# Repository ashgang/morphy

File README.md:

# Morphy
Contains the morphy design files and sources codes. The Hardware folder contains the schematics of various versions of the Morphy board and the associated evaluation board. The Software folder consists of the MorphyCore subfolder which contains the core morphy functionality, and the reference implementation of the client library for FreeRTOS.

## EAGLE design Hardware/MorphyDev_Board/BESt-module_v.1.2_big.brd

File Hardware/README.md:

# Morphy Hardware
MorphyPP3_board folder contains the design files for the Morphy PP3 form factor design.
MorphyDev_Board folder contains the design files of the development board for Morphy.

[All design documents including Board Schematics, PCB design and BOM sheets ]

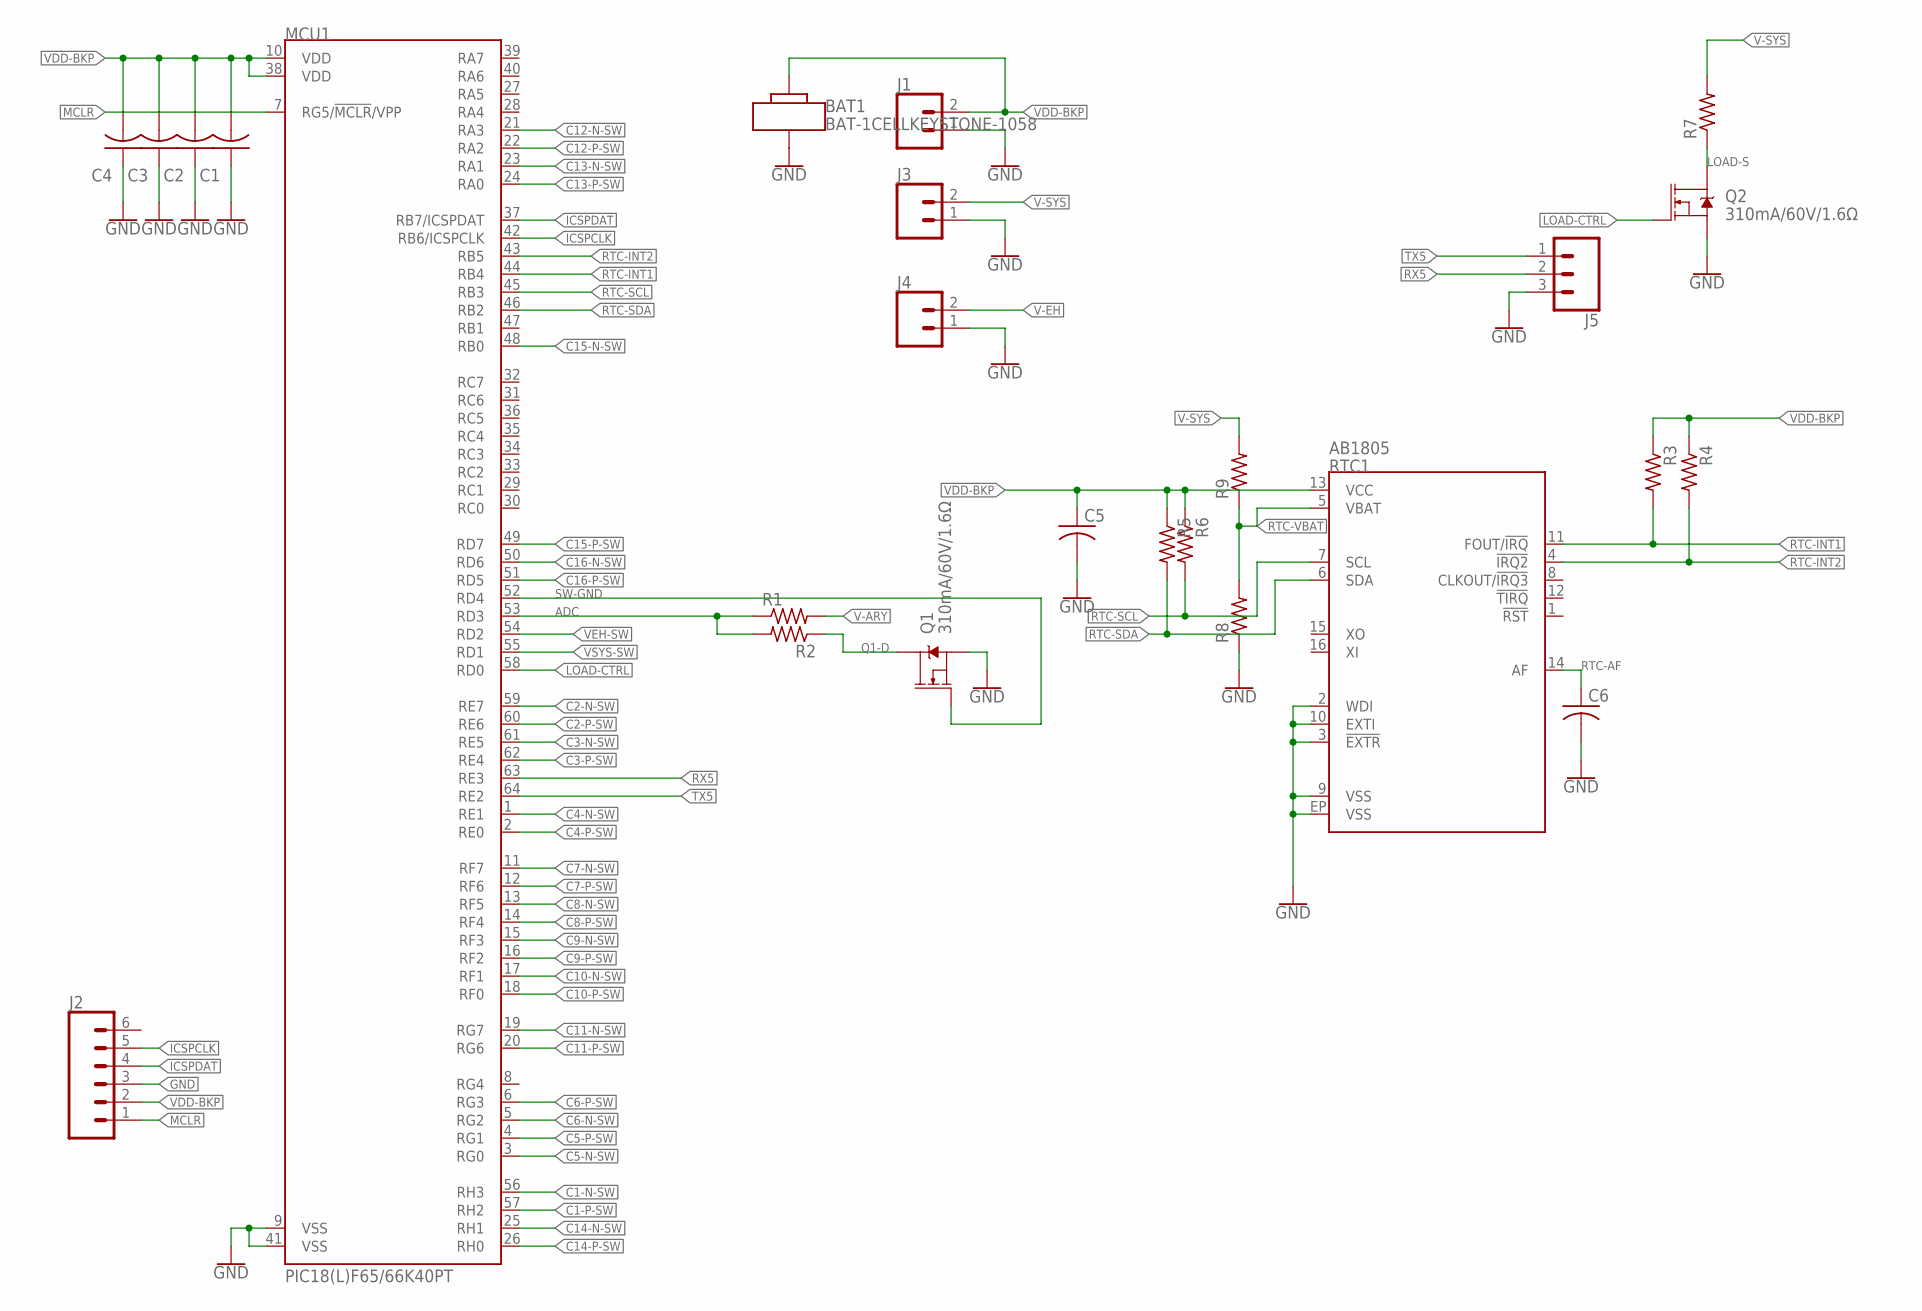
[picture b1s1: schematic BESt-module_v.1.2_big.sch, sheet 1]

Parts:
BAT1: BAT-1CELLKEYSTONE-1058; KEYSTONE-1058
C1, C2, C3, C4: 0.1uF; C0603
C5, C6: C-USC0603; C0603
J1: CONN_02; 1X02
J2: CONN_06NO_SILK_NO_POP; 1X06_NO_SILK
J3, J4: CONN_025MM; SCREWTERMINAL-5MM-2
J5: CONN_03; 1X03
MCU1: PIC18(L)F65/66K40PT; QFP50P1200X1200X120-64N
Q1, Q2: 310mA/60V/1.6Ω; SOT323
R1, R2, R3, R4, R5, R6, R8, R9: R-US_R0603; R0603
R7: R-US_R0805; R0805
RTC1: AB1805; QFN-16-3X3

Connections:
ADC: MCU1.53 (RD3), R1.1, R2.2
C1-N-SW: MCU1.56 (RH3); also elsewhere on the board
C1-P-SW: MCU1.57 (RH2); also elsewhere on the board
C2-N-SW: MCU1.59 (RE7); also elsewhere on the board
C2-P-SW: MCU1.60 (RE6); also elsewhere on the board
C3-N-SW: MCU1.61 (RE5); also elsewhere on the board
C3-P-SW: MCU1.62 (RE4); also elsewhere on the board
C4-N-SW: MCU1.1 (RE1); also elsewhere on the board
C4-P-SW: MCU1.2 (RE0); also elsewhere on the board
C5-N-SW: MCU1.3 (RG0); also elsewhere on the board
C5-P-SW: MCU1.4 (RG1); also elsewhere on the board
C6-N-SW: MCU1.5 (RG2); also elsewhere on the board
C6-P-SW: MCU1.6 (RG3); also elsewhere on the board
C7-N-SW: MCU1.11 (RF7); also elsewhere on the board
C7-P-SW: MCU1.12 (RF6); also elsewhere on the board
C8-N-SW: MCU1.13 (RF5); also elsewhere on the board
C8-P-SW: MCU1.14 (RF4); also elsewhere on the board
C9-N-SW: MCU1.15 (RF3); also elsewhere on the board
C9-P-SW: MCU1.16 (RF2); also elsewhere on the board
C10-N-SW: MCU1.17 (RF1); also elsewhere on the board
C10-P-SW: MCU1.18 (RF0); also elsewhere on the board
C11-N-SW: MCU1.19 (RG7); also elsewhere on the board
C11-P-SW: MCU1.20 (RG6); also elsewhere on the board
C12-N-SW: MCU1.21 (RA3); also elsewhere on the board
C12-P-SW: MCU1.22 (RA2); also elsewhere on the board
C13-N-SW: MCU1.23 (RA1); also elsewhere on the board
C13-P-SW: MCU1.24 (RA0); also elsewhere on the board
C14-N-SW: MCU1.25 (RH1); also elsewhere on the board
C14-P-SW: MCU1.26 (RH0); also elsewhere on the board
C15-N-SW: MCU1.48 (RB0); also elsewhere on the board
C15-P-SW: MCU1.49 (RD7); also elsewhere on the board
C16-N-SW: MCU1.50 (RD6); also elsewhere on the board
C16-P-SW: MCU1.51 (RD5); also elsewhere on the board
GND: BAT1.N, C1.1, C2.1, C3.1, C4.1, C5.2, C6.2, J1.1, J2.3, J3.1, J4.1, J5.3, MCU1.9 (VSS), MCU1.41 (VSS), Q1.2 (S), Q2.2 (S), R8.1, RTC1.2 (WDI), RTC1.3 (!EXTR), RTC1.9 (VSS), RTC1.10 (EXTI), RTC1.EP (VSS); also elsewhere on the board
ICSPCLK: J2.5, MCU1.42 (RB6/ICSPCLK)
ICSPDAT: J2.4, MCU1.37 (RB7/ICSPDAT)
LOAD-CTRL: MCU1.58 (RD0), Q2.1 (G)
LOAD-S: Q2.3 (D), R7.1
MCLR: J2.1, MCU1.7 (RG5/!MCLR!/VPP)
Q1-D: Q1.3 (D), R2.1
RTC-AF: C6.1, RTC1.14 (AF)
RTC-INT1: MCU1.44 (RB4), R3.2, RTC1.11 (FOUT/!IRQ)
RTC-INT2: MCU1.43 (RB5), R4.2, RTC1.4 (!IRQ2)
RTC-SCL: MCU1.45 (RB3), R6.2, RTC1.7 (SCL)
RTC-SDA: MCU1.46 (RB2), R5.2, RTC1.6 (SDA)
RTC-VBAT: R8.2, R9.1, RTC1.5 (VBAT)
RX5: J5.2, MCU1.63 (RE3)
SW-GND: MCU1.52 (RD4), Q1.1 (G)
TX5: J5.1, MCU1.64 (RE2)
V-ARY: R1.2; also elsewhere on the board
V-EH: J4.2; also elsewhere on the board
V-SYS: J3.2, R7.2, R9.2; also elsewhere on the board
VDD-BKP: BAT1.P, C1.2, C2.2, C3.2, C4.2, C5.1, J1.2, J2.2, MCU1.10 (VDD), MCU1.38 (VDD), R3.1, R4.1, R5.1, R6.1, RTC1.13 (VCC); also elsewhere on the board
VEH-SW: MCU1.54 (RD2); also elsewhere on the board
VSYS-SW: MCU1.55 (RD1); also elsewhere on the board

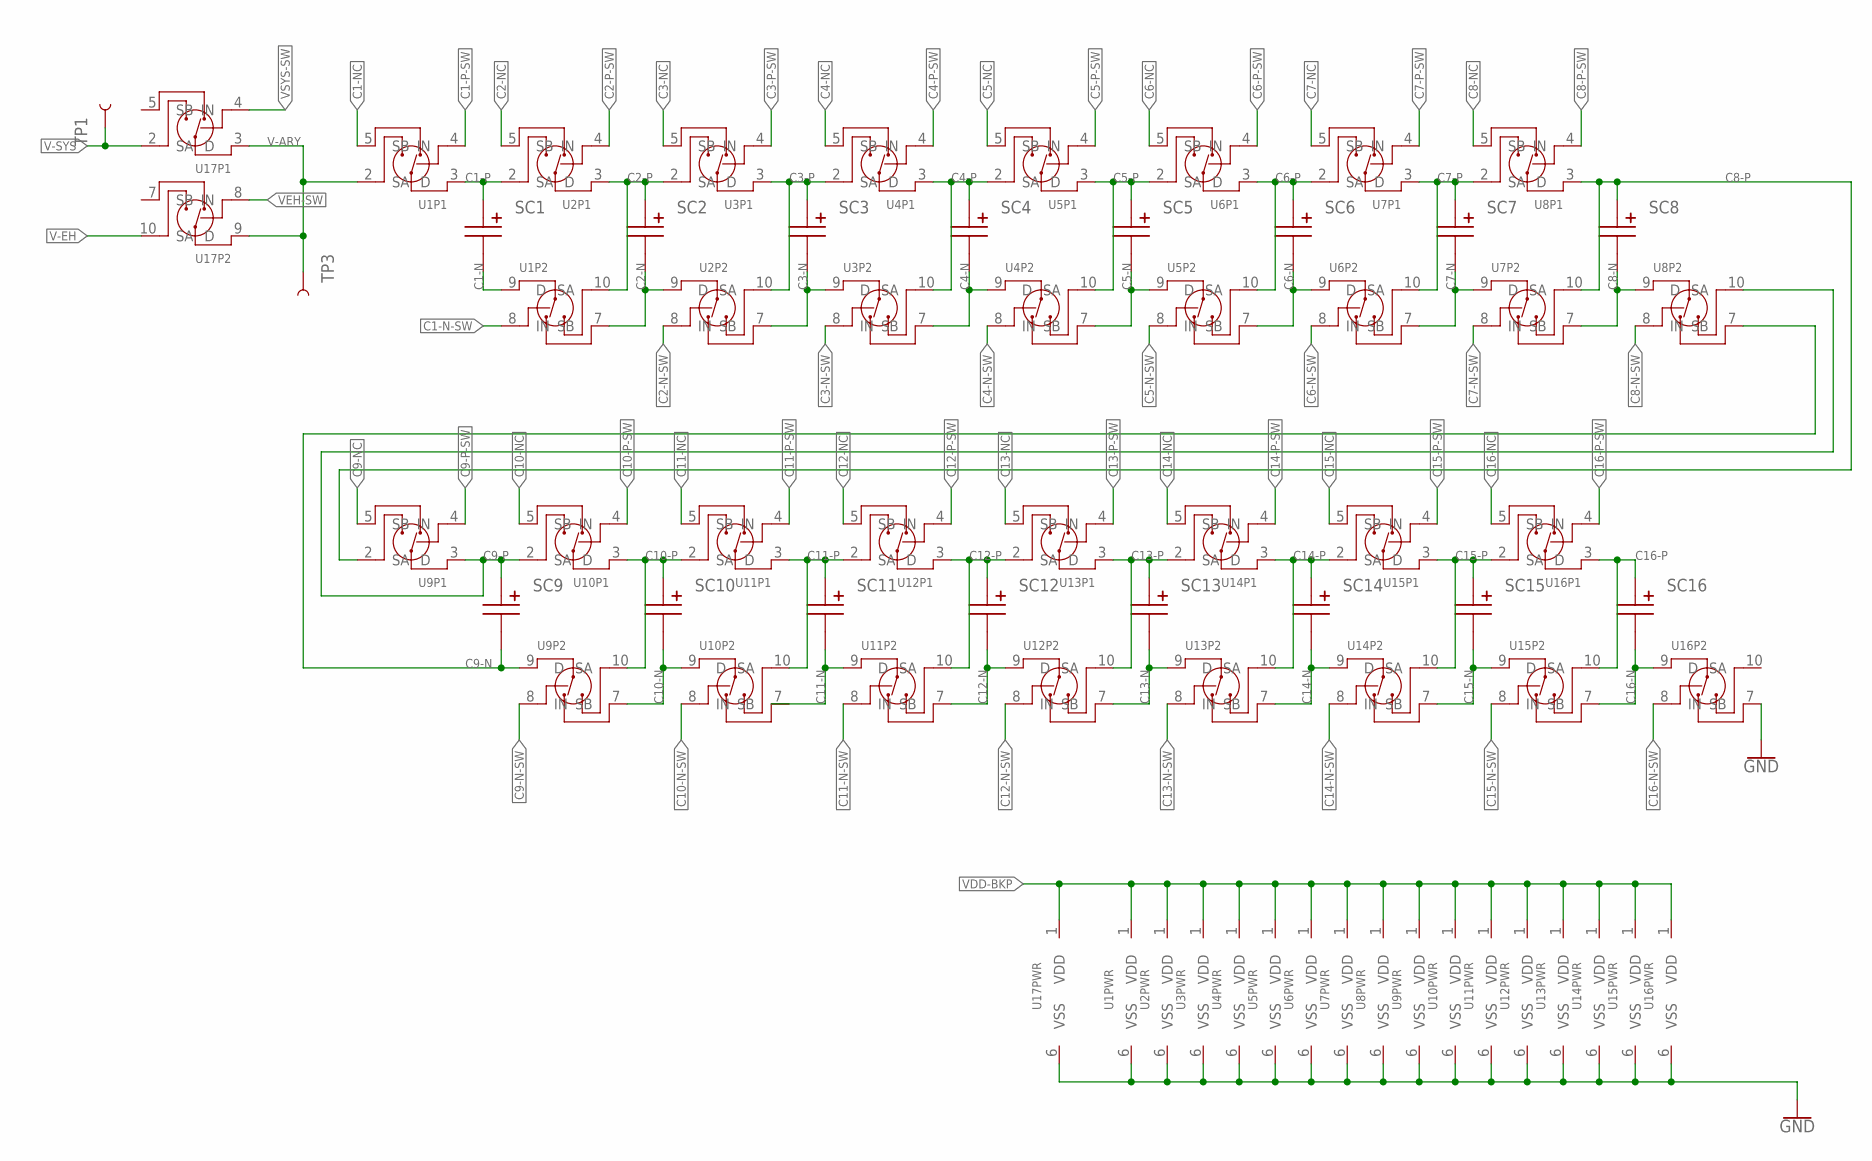
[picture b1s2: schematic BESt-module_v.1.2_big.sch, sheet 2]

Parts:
SC1, SC2, SC3, SC4, SC5, SC6, SC7, SC8, SC9, SC10, SC11, SC12, SC13, SC14, SC15, SC16: PM-5R0H/V104-R-VER; EATON-13X11.3X6-V
TP1, TP3: TEST-POINT3X4; PAD.03X.04
U1, U2, U3, U4, U5, U6, U7, U8, U9, U10, U11, U12, U13, U14, U15, U16, U17: DG2535EDQ; SOP50P490X110-10N

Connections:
C1-N: SC1.N, U1.9 (D)
C1-N-SW: U1.8 (IN); also elsewhere on the board
C1-NC: U1.5 (SB)
C1-P: SC1.P, U1.3 (D), U2.2 (SA)
C1-P-SW: U1.4 (IN); also elsewhere on the board
C2-N: SC2.N, U1.7 (SB), U2.9 (D)
C2-N-SW: U2.8 (IN); also elsewhere on the board
C2-NC: U2.5 (SB)
C2-P: SC2.P, U1.10 (SA), U2.3 (D), U3.2 (SA)
C2-P-SW: U2.4 (IN); also elsewhere on the board
C3-N: SC3.N, U2.7 (SB), U3.9 (D)
C3-N-SW: U3.8 (IN); also elsewhere on the board
C3-NC: U3.5 (SB)
C3-P: SC3.P, U2.10 (SA), U3.3 (D), U4.2 (SA)
C3-P-SW: U3.4 (IN); also elsewhere on the board
C4-N: SC4.N, U3.7 (SB), U4.9 (D)
C4-N-SW: U4.8 (IN); also elsewhere on the board
C4-NC: U4.5 (SB)
C4-P: SC4.P, U3.10 (SA), U4.3 (D), U5.2 (SA)
C4-P-SW: U4.4 (IN); also elsewhere on the board
C5-N: SC5.N, U4.7 (SB), U5.9 (D)
C5-N-SW: U5.8 (IN); also elsewhere on the board
C5-NC: U5.5 (SB)
C5-P: SC5.P, U4.10 (SA), U5.3 (D), U6.2 (SA)
C5-P-SW: U5.4 (IN); also elsewhere on the board
C6-N: SC6.N, U5.7 (SB), U6.9 (D)
C6-N-SW: U6.8 (IN); also elsewhere on the board
C6-NC: U6.5 (SB)
C6-P: SC6.P, U5.10 (SA), U6.3 (D), U7.2 (SA)
C6-P-SW: U6.4 (IN); also elsewhere on the board
C7-N: SC7.N, U6.7 (SB), U7.9 (D)
C7-N-SW: U7.8 (IN); also elsewhere on the board
C7-NC: U7.5 (SB)
C7-P: SC7.P, U6.10 (SA), U7.3 (D), U8.2 (SA)
C7-P-SW: U7.4 (IN); also elsewhere on the board
C8-N: SC8.N, U7.7 (SB), U8.9 (D)
C8-N-SW: U8.8 (IN); also elsewhere on the board
C8-NC: U8.5 (SB)
C8-P: SC8.P, U7.10 (SA), U8.3 (D), U9.2 (SA)
C8-P-SW: U8.4 (IN); also elsewhere on the board
C9-N: SC9.N, U8.7 (SB), U9.9 (D)
C9-N-SW: U9.8 (IN); also elsewhere on the board
C9-NC: U9.5 (SB)
C9-P: SC9.P, U8.10 (SA), U9.3 (D), U10.2 (SA)
C9-P-SW: U9.4 (IN); also elsewhere on the board
C10-N: SC10.N, U9.7 (SB), U10.9 (D)
C10-N-SW: U10.8 (IN); also elsewhere on the board
C10-NC: U10.5 (SB)
C10-P: SC10.P, U9.10 (SA), U10.3 (D), U11.2 (SA)
C10-P-SW: U10.4 (IN); also elsewhere on the board
C11-N: SC11.N, U10.7 (SB), U11.9 (D)
C11-N-SW: U11.8 (IN); also elsewhere on the board
C11-NC: U11.5 (SB)
C11-P: SC11.P, U10.10 (SA), U11.3 (D), U12.2 (SA)
C11-P-SW: U11.4 (IN); also elsewhere on the board
C12-N: SC12.N, U11.7 (SB), U12.9 (D)
C12-N-SW: U12.8 (IN); also elsewhere on the board
C12-NC: U12.5 (SB)
C12-P: SC12.P, U11.10 (SA), U12.3 (D), U13.2 (SA)
C12-P-SW: U12.4 (IN); also elsewhere on the board
C13-N: SC13.N, U12.7 (SB), U13.9 (D)
C13-N-SW: U13.8 (IN); also elsewhere on the board
C13-NC: U13.5 (SB)
C13-P: SC13.P, U12.10 (SA), U13.3 (D), U14.2 (SA)
C13-P-SW: U13.4 (IN); also elsewhere on the board
C14-N: SC14.N, U13.7 (SB), U14.9 (D)
C14-N-SW: U14.8 (IN); also elsewhere on the board
C14-NC: U14.5 (SB)
C14-P: SC14.P, U13.10 (SA), U14.3 (D), U15.2 (SA)
C14-P-SW: U14.4 (IN); also elsewhere on the board
C15-N: SC15.N, U14.7 (SB), U15.9 (D)
C15-N-SW: U15.8 (IN); also elsewhere on the board
C15-NC: U15.5 (SB)
C15-P: SC15.P, U14.10 (SA), U15.3 (D), U16.2 (SA)
C15-P-SW: U15.4 (IN); also elsewhere on the board
C16-N: SC16.N, U15.7 (SB), U16.9 (D)
C16-N-SW: U16.8 (IN); also elsewhere on the board
C16-NC: U16.5 (SB)
C16-P: SC16.P, U15.10 (SA), U16.3 (D)
C16-P-SW: U16.4 (IN); also elsewhere on the board
GND: U1.6 (VSS), U2.6 (VSS), U3.6 (VSS), U4.6 (VSS), U5.6 (VSS), U6.6 (VSS), U7.6 (VSS), U8.6 (VSS), U9.6 (VSS), U10.6 (VSS), U11.6 (VSS), U12.6 (VSS), U13.6 (VSS), U14.6 (VSS), U15.6 (VSS), U16.6 (VSS), U16.7 (SB), U17.6 (VSS); also elsewhere on the board
V-ARY: TP3.P$1, U1.2 (SA), U17.3 (D), U17.9 (D); also elsewhere on the board
V-EH: U17.10 (SA); also elsewhere on the board
V-SYS: TP1.P$1, U17.2 (SA); also elsewhere on the board
VDD-BKP: U1.1 (VDD), U2.1 (VDD), U3.1 (VDD), U4.1 (VDD), U5.1 (VDD), U6.1 (VDD), U7.1 (VDD), U8.1 (VDD), U9.1 (VDD), U10.1 (VDD), U11.1 (VDD), U12.1 (VDD), U13.1 (VDD), U14.1 (VDD), U15.1 (VDD), U16.1 (VDD), U17.1 (VDD); also elsewhere on the board
VEH-SW: U17.8 (IN); also elsewhere on the board
VSYS-SW: U17.4 (IN); also elsewhere on the board

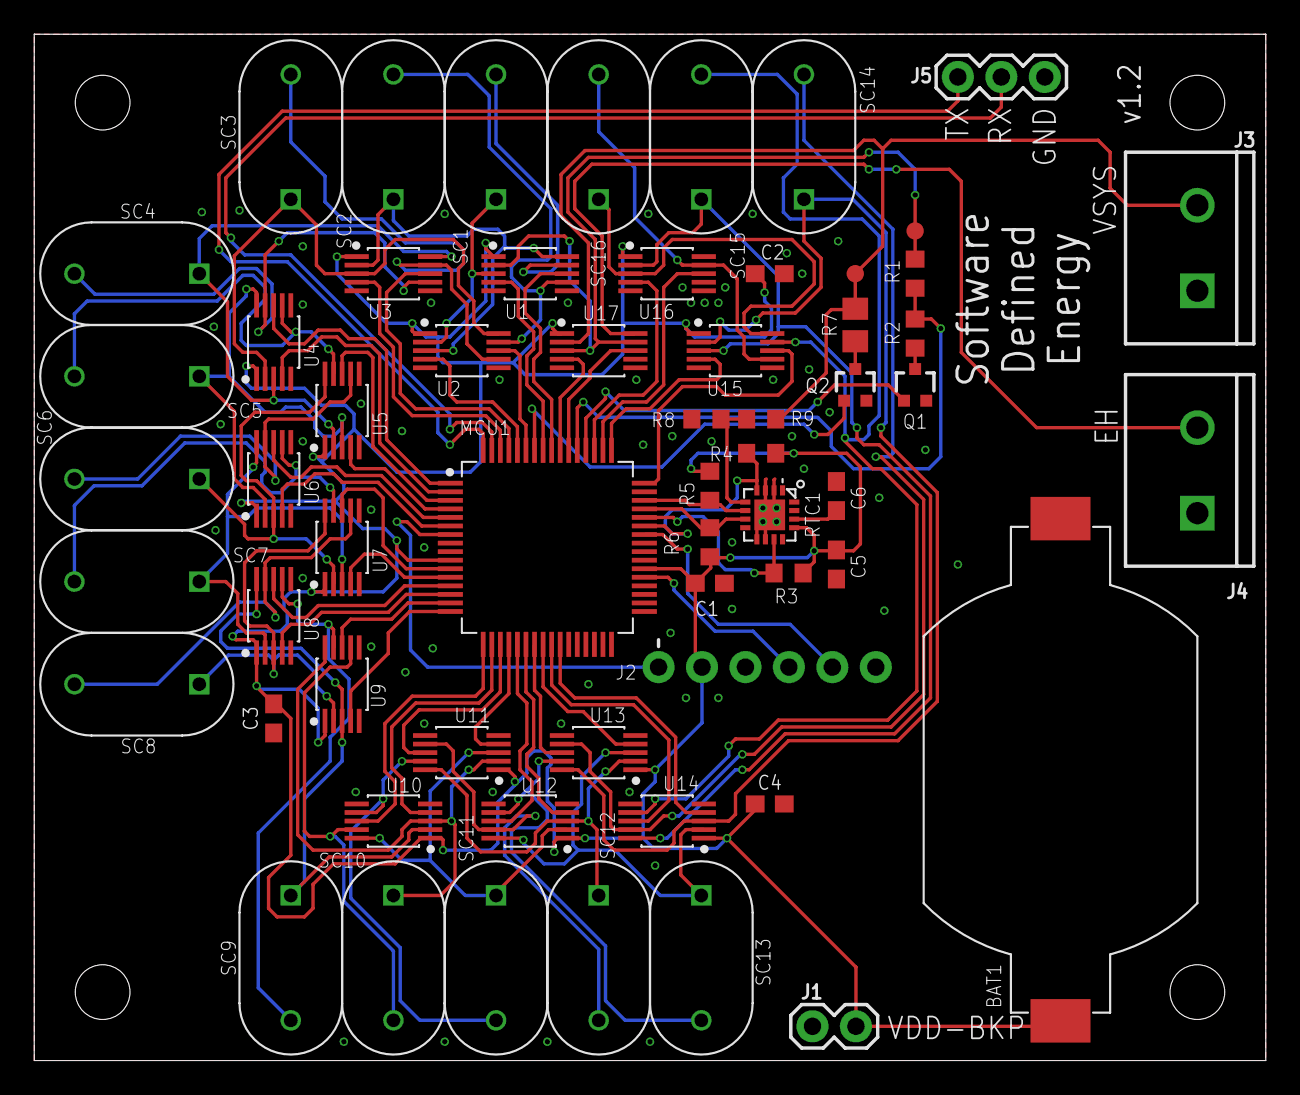
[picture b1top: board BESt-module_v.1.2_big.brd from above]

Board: 2 copper layers, 72.0 x 60.0 mm, 60 parts (0 on the bottom side), 87 nets.

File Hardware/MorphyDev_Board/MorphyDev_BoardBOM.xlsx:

Comment | Description | Designator | Footprint | LibRef | Quantity
BAT-1CELLKEYSTONE-1058 |  | BAT1 | KEYSTONE-1058 | BAT-1CELLKEYSTONE-1058 | 1
0.1uF | CAPACITOR, American symbol | C1, C2, C3, C4 | C0603 | C-USC0603 | 4
C-USC0603 | CAPACITOR, American symbol | C5, C6 | C0603 | C-USC0603 | 2
CONN_02 | Multi connection point. Often used as Generic Header-pin footprint for 0.1 inch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 | J1 | 1X02 | CONN_02 | 1
CONN_06NO_SILK_NO_POP | Multi connection point. Often used as Generic Header-pin footprint for 0.1 inch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 | J2 | 1X06_NO_SILK | CONN_06NO_SILK_NO_POP | 1
CONN_025MM | Multi connection point. Often used as Generic Header-pin footprint for 0.1 inch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 | J3, J4 | SCREWTERMINAL-5MM-2 | CONN_025MM | 2
CONN_03 | Multi connection point. Often used as Generic Header-pin footprint for 0.1 inch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 | J5 | 1X03 | CONN_03 | 1
PIC18(L)F65/66K40PT | 64-Pin, Low-Power, High-Performance Microcontrollers with XLP Technology | MCU1 | QFP50P1200X1200X120-64N | PIC18(L)F65/66K40PT | 1
310mA/60V/1.6Ω | N-channel MOSFETs Voltage controlled devices that allow control of high current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 | Q1, Q2 | SOT323 | MOSFET-NCH-2N7002PW | 2
R-US_R0603 | RESISTOR, American symbol | R1, R2, R3, R4, R5, R6, R8, R9 | R0603 | R-US_R0603 | 8
R-US_R0805 | RESISTOR, American symbol | R7 | R0805 | R-US_R0805 | 1
AB1805 |  | RTC1 | QFN-16-3X3 | AB1805 | 1
PM-5R0H/V104-R-VER | CAP 100MF -20% +80% 5V T/H | SC1, SC2, SC3, SC4, SC5, SC6, SC7, SC8, SC9, SC10, SC11, SC12, SC13, SC14, SC15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 | EATON-13X11.3X6-V | PM-5R0H/V104-R-VER | 16
TEST-POINT3X4 | SparkFun Test Points Bare copper test points for troubleshooting or In-Circuit-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 | TP1, TP3 | PAD.03X.04 | TEST-POINT3X4 | 2
DG2535EDQ | IC ANALOG SWITCH DUAL | U1, U2, U3, U4, U5, U6, U7, U8, U9, U10, U11, U12, U13, U14, U15, U16, U17 | SOP50P490X110-10N | DG2535EDQ | 17

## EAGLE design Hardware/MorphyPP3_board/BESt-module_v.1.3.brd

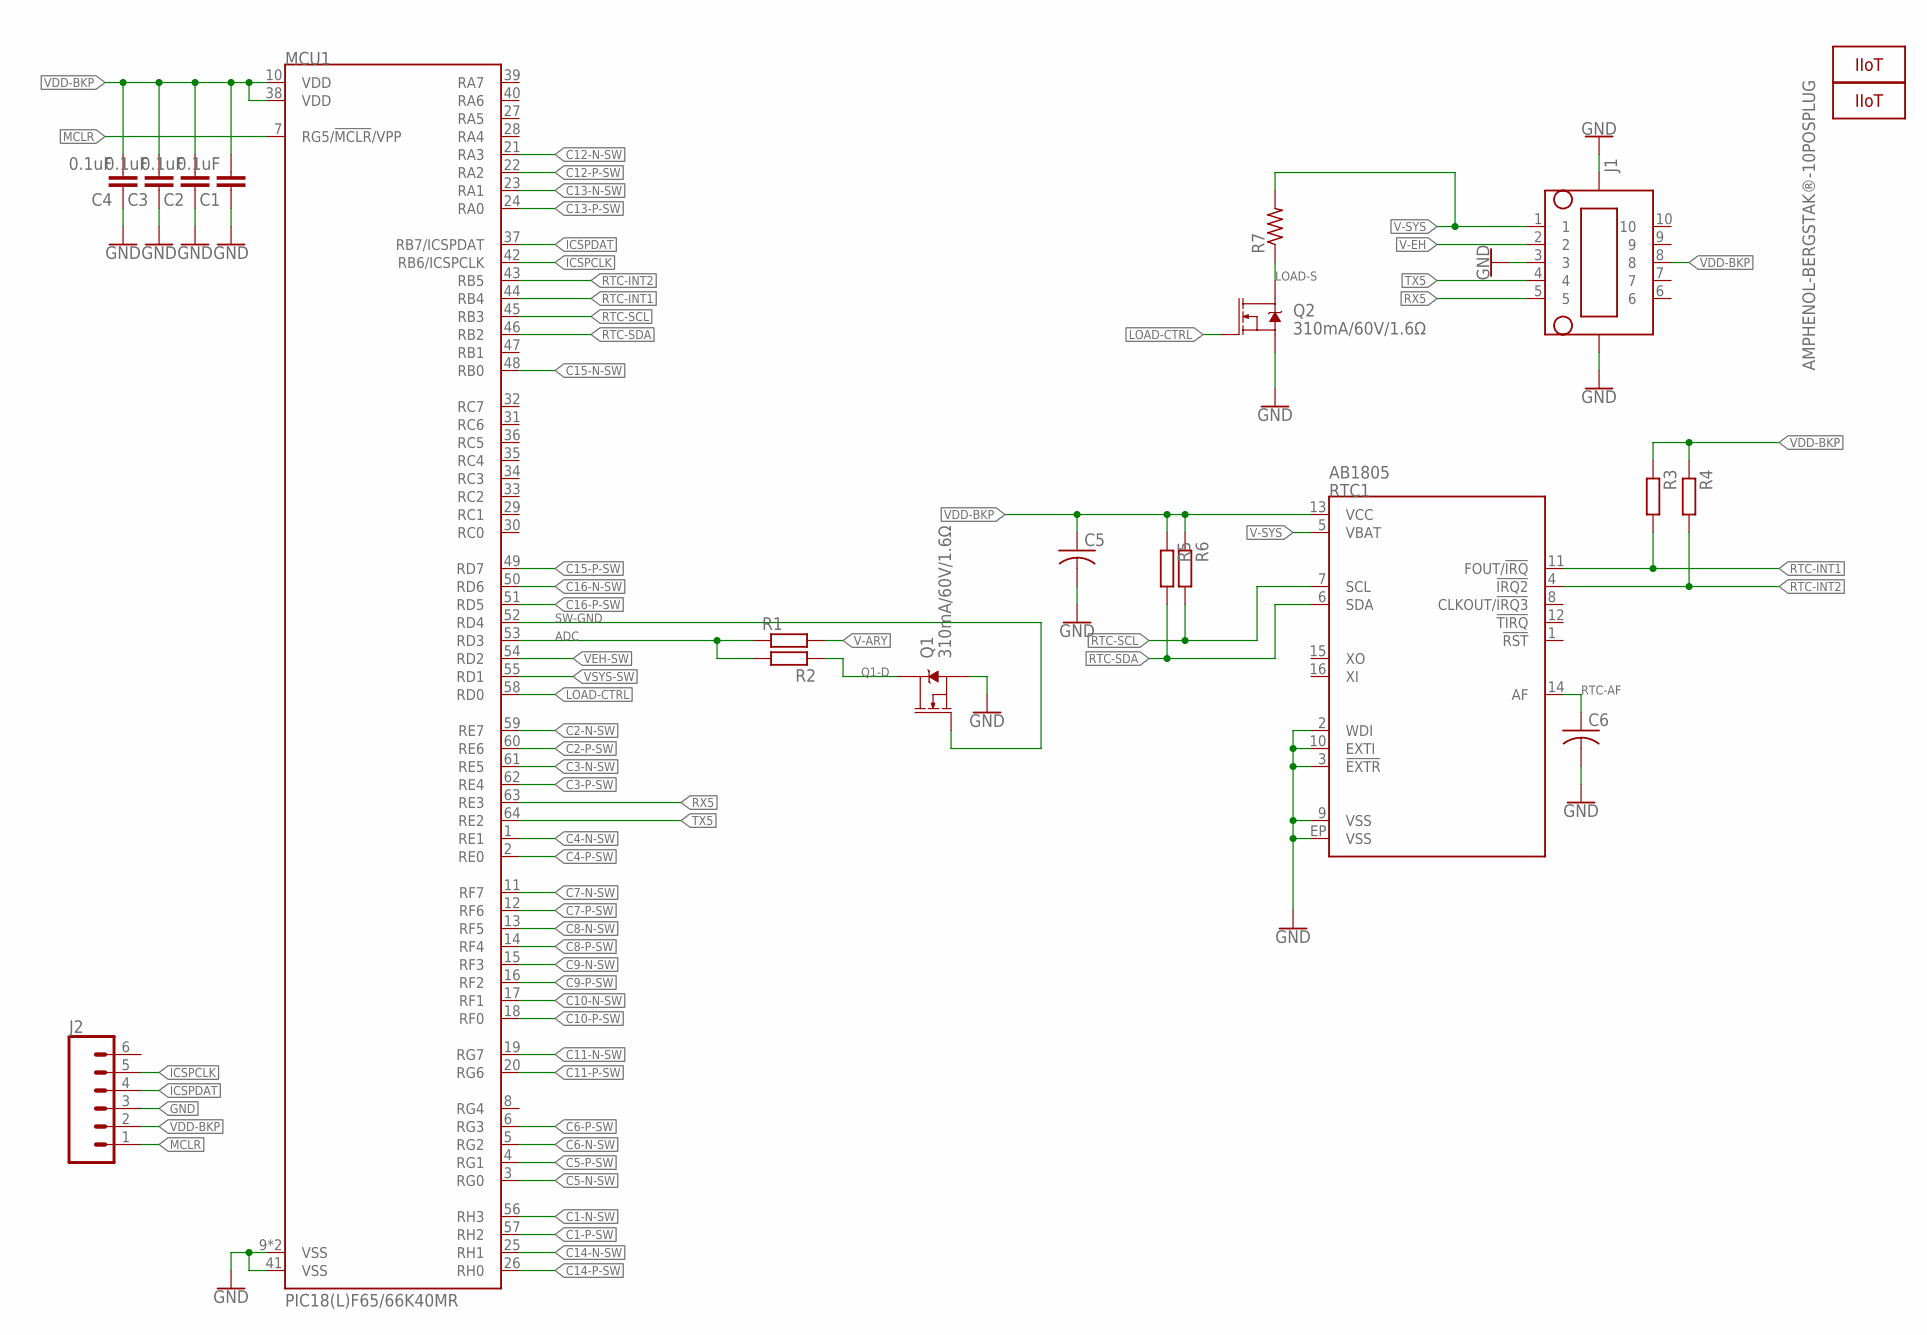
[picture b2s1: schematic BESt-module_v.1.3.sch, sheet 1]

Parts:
C1, C2, C3, C4: 0.1uF; 0603
C5, C6: C-USC0402; C0402
J1: AMPHENOL-BERGSTAK®-10POSPLUG; 10132797-10POS-PLUG
J2: CONN_06NO_SILK_NO_POP; 1X06_NO_SILK
LOGO1, LOGO2: IIOT
MCU1: PIC18(L)F65/66K40MR; QFN50P900X900X100-65T715N
Q1, Q2: 310mA/60V/1.6Ω; SOT323
R1, R2, R3, R4, R5, R6: R-EU_R0402; R0402
R7: R-US_R0805; R0805
RTC1: AB1805; QFN-16-3X3

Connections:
ADC: MCU1.53 (RD3), R1.1, R2.2
C1-N-SW: MCU1.56 (RH3); also elsewhere on the board
C1-P-SW: MCU1.57 (RH2); also elsewhere on the board
C2-N-SW: MCU1.59 (RE7); also elsewhere on the board
C2-P-SW: MCU1.60 (RE6); also elsewhere on the board
C3-N-SW: MCU1.61 (RE5); also elsewhere on the board
C3-P-SW: MCU1.62 (RE4); also elsewhere on the board
C4-N-SW: MCU1.1 (RE1); also elsewhere on the board
C4-P-SW: MCU1.2 (RE0); also elsewhere on the board
C5-N-SW: MCU1.3 (RG0); also elsewhere on the board
C5-P-SW: MCU1.4 (RG1); also elsewhere on the board
C6-N-SW: MCU1.5 (RG2); also elsewhere on the board
C6-P-SW: MCU1.6 (RG3); also elsewhere on the board
C7-N-SW: MCU1.11 (RF7); also elsewhere on the board
C7-P-SW: MCU1.12 (RF6); also elsewhere on the board
C8-N-SW: MCU1.13 (RF5); also elsewhere on the board
C8-P-SW: MCU1.14 (RF4); also elsewhere on the board
C9-N-SW: MCU1.15 (RF3); also elsewhere on the board
C9-P-SW: MCU1.16 (RF2); also elsewhere on the board
C10-N-SW: MCU1.17 (RF1); also elsewhere on the board
C10-P-SW: MCU1.18 (RF0); also elsewhere on the board
C11-N-SW: MCU1.19 (RG7); also elsewhere on the board
C11-P-SW: MCU1.20 (RG6); also elsewhere on the board
C12-N-SW: MCU1.21 (RA3); also elsewhere on the board
C12-P-SW: MCU1.22 (RA2); also elsewhere on the board
C13-N-SW: MCU1.23 (RA1); also elsewhere on the board
C13-P-SW: MCU1.24 (RA0); also elsewhere on the board
C14-N-SW: MCU1.25 (RH1); also elsewhere on the board
C14-P-SW: MCU1.26 (RH0); also elsewhere on the board
C15-N-SW: MCU1.48 (RB0); also elsewhere on the board
C15-P-SW: MCU1.49 (RD7); also elsewhere on the board
C16-N-SW: MCU1.50 (RD6); also elsewhere on the board
C16-P-SW: MCU1.51 (RD5); also elsewhere on the board
GND: C1.1, C2.1, C3.1, C4.1, C5.2, C6.2, J1.3, J1.MNT1, J1.MNT2, J2.3, MCU1.9 (VSS), MCU1.41 (VSS), MCU1.65 (VSS), Q1.2 (S), Q2.2 (S), RTC1.2 (WDI), RTC1.3 (!EXTR), RTC1.9 (VSS), RTC1.10 (EXTI), RTC1.EP (VSS); also elsewhere on the board
ICSPCLK: J2.5, MCU1.42 (RB6/ICSPCLK)
ICSPDAT: J2.4, MCU1.37 (RB7/ICSPDAT)
LOAD-CTRL: MCU1.58 (RD0), Q2.1 (G)
LOAD-S: Q2.3 (D), R7.1
MCLR: J2.1, MCU1.7 (RG5/!MCLR!/VPP)
Q1-D: Q1.3 (D), R2.1
RTC-AF: C6.1, RTC1.14 (AF)
RTC-INT1: MCU1.44 (RB4), R3.2, RTC1.11 (FOUT/!IRQ)
RTC-INT2: MCU1.43 (RB5), R4.2, RTC1.4 (!IRQ2)
RTC-SCL: MCU1.45 (RB3), R6.2, RTC1.7 (SCL)
RTC-SDA: MCU1.46 (RB2), R5.2, RTC1.6 (SDA)
RX5: J1.5, MCU1.63 (RE3)
SW-GND: MCU1.52 (RD4), Q1.1 (G)
TX5: J1.4, MCU1.64 (RE2)
V-ARY: R1.2; also elsewhere on the board
V-EH: J1.2; also elsewhere on the board
V-SYS: J1.1, R7.2, RTC1.5 (VBAT); also elsewhere on the board
VDD-BKP: C1.2, C2.2, C3.2, C4.2, C5.1, J1.8, J2.2, MCU1.10 (VDD), MCU1.38 (VDD), R3.1, R4.1, R5.1, R6.1, RTC1.13 (VCC); also elsewhere on the board
VEH-SW: MCU1.54 (RD2); also elsewhere on the board
VSYS-SW: MCU1.55 (RD1); also elsewhere on the board

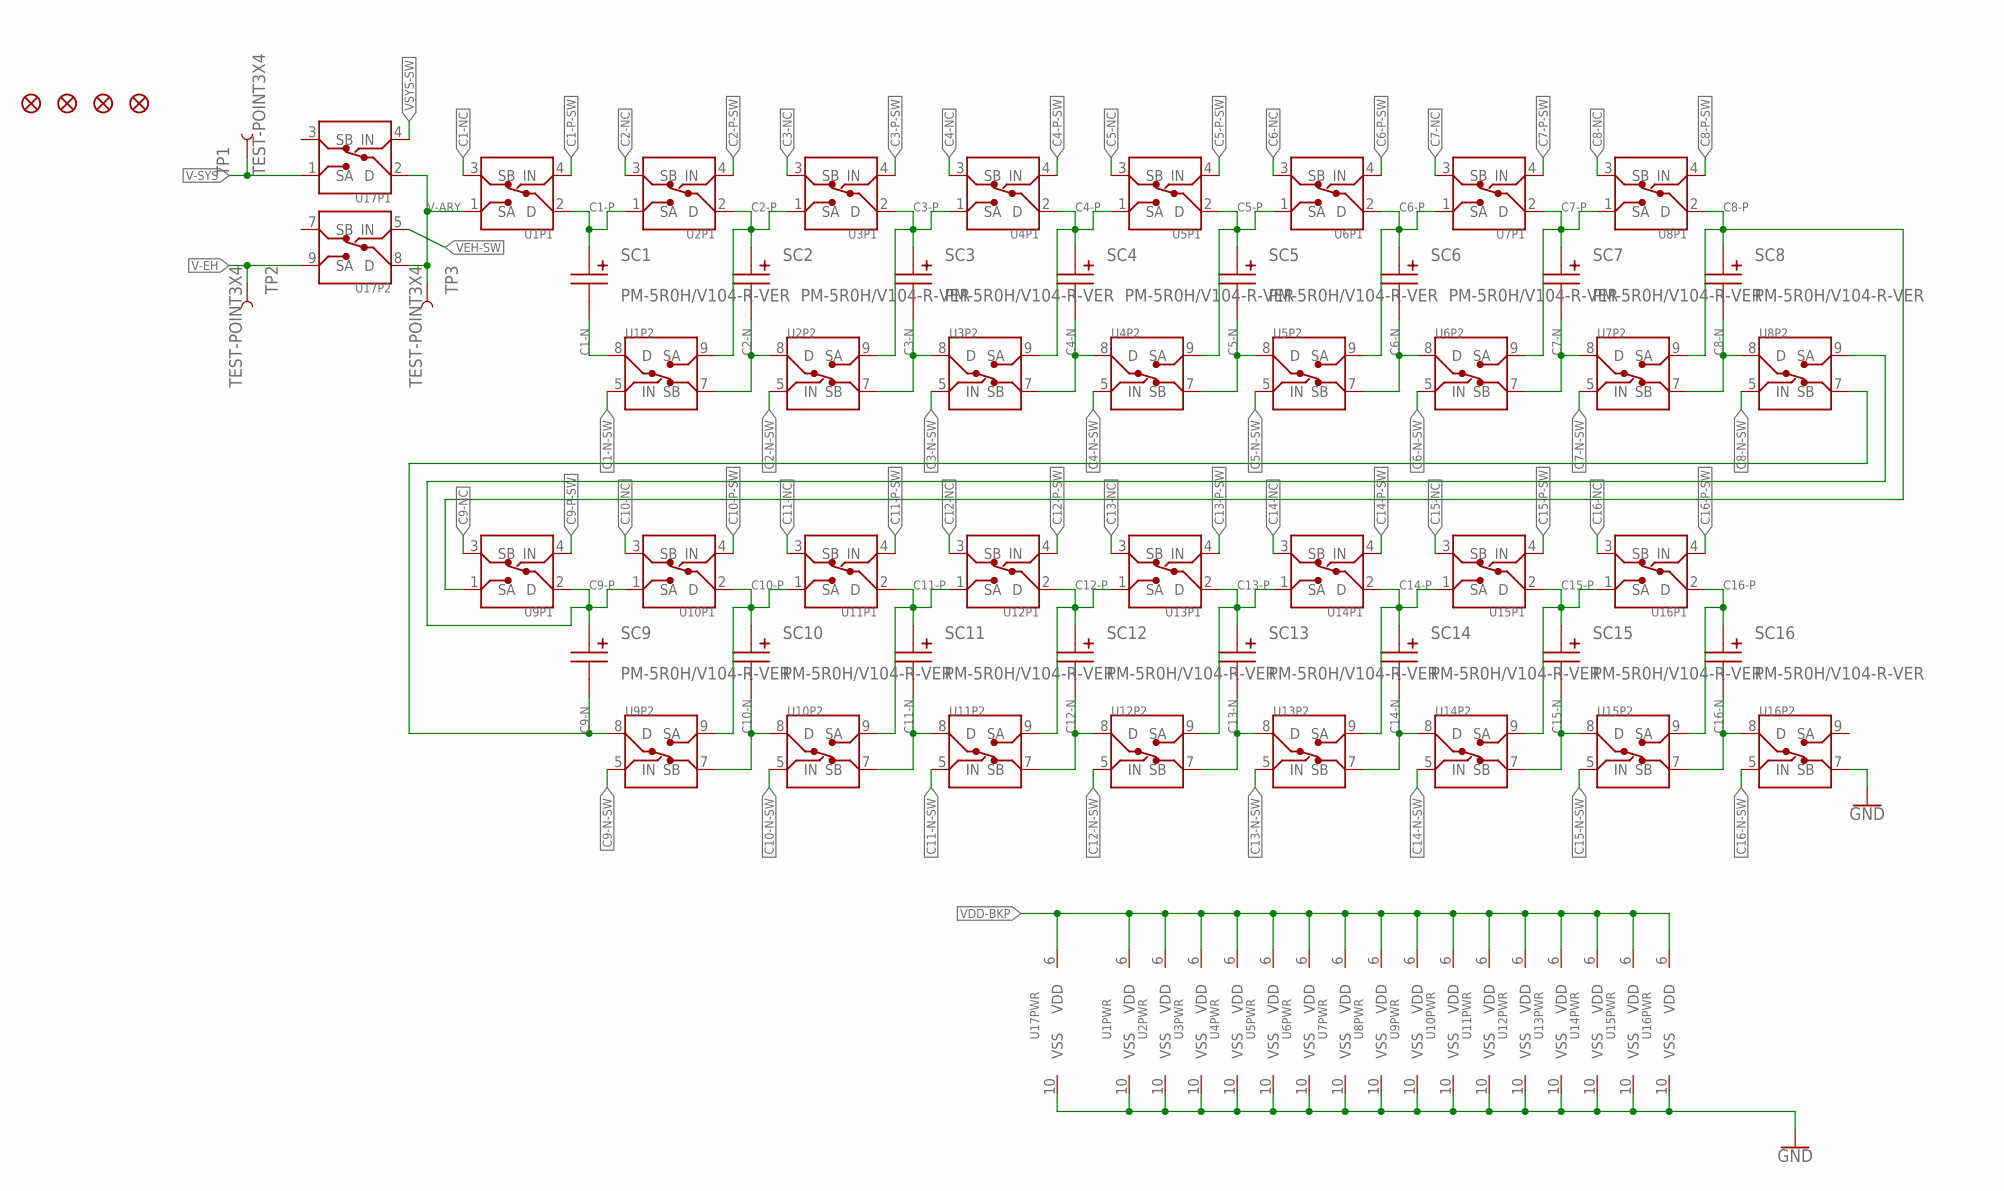
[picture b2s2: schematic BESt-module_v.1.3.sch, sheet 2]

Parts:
FD1, FD2, FD3, FD4: FIDUCIAL1X2; FIDUCIAL-1X2
SC1, SC2, SC3, SC4, SC5, SC6, SC7, SC8, SC9, SC10, SC11, SC12, SC13, SC14, SC15, SC16: PM-5R0H/V104-R-VER; EATON-13X11.3X6-V
TP1, TP2, TP3: TEST-POINT3X4; PAD.03X.04
U1, U2, U3, U4, U5, U6, U7, U8, U9, U10, U11, U12, U13, U14, U15, U16, U17: ADG824; CP-10-10

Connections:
C1-N: SC1.N, U1.8 (D)
C1-N-SW: U1.5 (IN); also elsewhere on the board
C1-NC: U1.3 (SB)
C1-P: SC1.P, U1.2 (D), U2.1 (SA)
C1-P-SW: U1.4 (IN); also elsewhere on the board
C2-N: SC2.N, U1.7 (SB), U2.8 (D)
C2-N-SW: U2.5 (IN); also elsewhere on the board
C2-NC: U2.3 (SB)
C2-P: SC2.P, U1.9 (SA), U2.2 (D), U3.1 (SA)
C2-P-SW: U2.4 (IN); also elsewhere on the board
C3-N: SC3.N, U2.7 (SB), U3.8 (D)
C3-N-SW: U3.5 (IN); also elsewhere on the board
C3-NC: U3.3 (SB)
C3-P: SC3.P, U2.9 (SA), U3.2 (D), U4.1 (SA)
C3-P-SW: U3.4 (IN); also elsewhere on the board
C4-N: SC4.N, U3.7 (SB), U4.8 (D)
C4-N-SW: U4.5 (IN); also elsewhere on the board
C4-NC: U4.3 (SB)
C4-P: SC4.P, U3.9 (SA), U4.2 (D), U5.1 (SA)
C4-P-SW: U4.4 (IN); also elsewhere on the board
C5-N: SC5.N, U4.7 (SB), U5.8 (D)
C5-N-SW: U5.5 (IN); also elsewhere on the board
C5-NC: U5.3 (SB)
C5-P: SC5.P, U4.9 (SA), U5.2 (D), U6.1 (SA)
C5-P-SW: U5.4 (IN); also elsewhere on the board
C6-N: SC6.N, U5.7 (SB), U6.8 (D)
C6-N-SW: U6.5 (IN); also elsewhere on the board
C6-NC: U6.3 (SB)
C6-P: SC6.P, U5.9 (SA), U6.2 (D), U7.1 (SA)
C6-P-SW: U6.4 (IN); also elsewhere on the board
C7-N: SC7.N, U6.7 (SB), U7.8 (D)
C7-N-SW: U7.5 (IN); also elsewhere on the board
C7-NC: U7.3 (SB)
C7-P: SC7.P, U6.9 (SA), U7.2 (D), U8.1 (SA)
C7-P-SW: U7.4 (IN); also elsewhere on the board
C8-N: SC8.N, U7.7 (SB), U8.8 (D)
C8-N-SW: U8.5 (IN); also elsewhere on the board
C8-NC: U8.3 (SB)
C8-P: SC8.P, U7.9 (SA), U8.2 (D), U9.1 (SA)
C8-P-SW: U8.4 (IN); also elsewhere on the board
C9-N: SC9.N, U8.7 (SB), U9.8 (D)
C9-N-SW: U9.5 (IN); also elsewhere on the board
C9-NC: U9.3 (SB)
C9-P: SC9.P, U8.9 (SA), U9.2 (D), U10.1 (SA)
C9-P-SW: U9.4 (IN); also elsewhere on the board
C10-N: SC10.N, U9.7 (SB), U10.8 (D)
C10-N-SW: U10.5 (IN); also elsewhere on the board
C10-NC: U10.3 (SB)
C10-P: SC10.P, U9.9 (SA), U10.2 (D), U11.1 (SA)
C10-P-SW: U10.4 (IN); also elsewhere on the board
C11-N: SC11.N, U10.7 (SB), U11.8 (D)
C11-N-SW: U11.5 (IN); also elsewhere on the board
C11-NC: U11.3 (SB)
C11-P: SC11.P, U10.9 (SA), U11.2 (D), U12.1 (SA)
C11-P-SW: U11.4 (IN); also elsewhere on the board
C12-N: SC12.N, U11.7 (SB), U12.8 (D)
C12-N-SW: U12.5 (IN); also elsewhere on the board
C12-NC: U12.3 (SB)
C12-P: SC12.P, U11.9 (SA), U12.2 (D), U13.1 (SA)
C12-P-SW: U12.4 (IN); also elsewhere on the board
C13-N: SC13.N, U12.7 (SB), U13.8 (D)
C13-N-SW: U13.5 (IN); also elsewhere on the board
C13-NC: U13.3 (SB)
C13-P: SC13.P, U12.9 (SA), U13.2 (D), U14.1 (SA)
C13-P-SW: U13.4 (IN); also elsewhere on the board
C14-N: SC14.N, U13.7 (SB), U14.8 (D)
C14-N-SW: U14.5 (IN); also elsewhere on the board
C14-NC: U14.3 (SB)
C14-P: SC14.P, U13.9 (SA), U14.2 (D), U15.1 (SA)
C14-P-SW: U14.4 (IN); also elsewhere on the board
C15-N: SC15.N, U14.7 (SB), U15.8 (D)
C15-N-SW: U15.5 (IN); also elsewhere on the board
C15-NC: U15.3 (SB)
C15-P: SC15.P, U14.9 (SA), U15.2 (D), U16.1 (SA)
C15-P-SW: U15.4 (IN); also elsewhere on the board
C16-N: SC16.N, U15.7 (SB), U16.8 (D)
C16-N-SW: U16.5 (IN); also elsewhere on the board
C16-NC: U16.3 (SB)
C16-P: SC16.P, U15.9 (SA), U16.2 (D)
C16-P-SW: U16.4 (IN); also elsewhere on the board
GND: U1.10 (VSS), U2.10 (VSS), U3.10 (VSS), U4.10 (VSS), U5.10 (VSS), U6.10 (VSS), U7.10 (VSS), U8.10 (VSS), U9.10 (VSS), U10.10 (VSS), U11.10 (VSS), U12.10 (VSS), U13.10 (VSS), U14.10 (VSS), U15.10 (VSS), U16.7 (SB), U16.10 (VSS), U17.10 (VSS); also elsewhere on the board
V-ARY: TP3.P$1, U1.1 (SA), U17.2 (D), U17.8 (D); also elsewhere on the board
V-EH: TP2.P$1, U17.9 (SA); also elsewhere on the board
V-SYS: TP1.P$1, U17.1 (SA); also elsewhere on the board
VDD-BKP: U1.6 (VDD), U2.6 (VDD), U3.6 (VDD), U4.6 (VDD), U5.6 (VDD), U6.6 (VDD), U7.6 (VDD), U8.6 (VDD), U9.6 (VDD), U10.6 (VDD), U11.6 (VDD), U12.6 (VDD), U13.6 (VDD), U14.6 (VDD), U15.6 (VDD), U16.6 (VDD), U17.6 (VDD); also elsewhere on the board
VEH-SW: U17.5 (IN); also elsewhere on the board
VSYS-SW: U17.4 (IN); also elsewhere on the board

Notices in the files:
Software/Morphycore/Morphycore/mcc_generated_files/pin_manager.h:
(c) 2018 Microchip Technology Inc. and its subsidiaries.
parts and their libraries:
SparkFun-Connectors: Licensing: Creative Commons ShareAlike 4.0 International - https://creativecommons.org/licenses/by-sa/4.0
